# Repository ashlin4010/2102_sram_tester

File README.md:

# 2102 SRAM Tester #

A basic tester to quickly check 2102 RAM chips. This tester only performs rudimentary tests and is very lax with its timing so it may not fully detect marginal RAM chips.

## Firmware ##
The firmware is a quick and dirty Arduino program and makes use of `digitalWrite` and is subsequently very slow. Things could be sped up significantly by writing the firmware in AVR and using timers and cycle counting. The circuit would also benefit from an external latch for the address lines.

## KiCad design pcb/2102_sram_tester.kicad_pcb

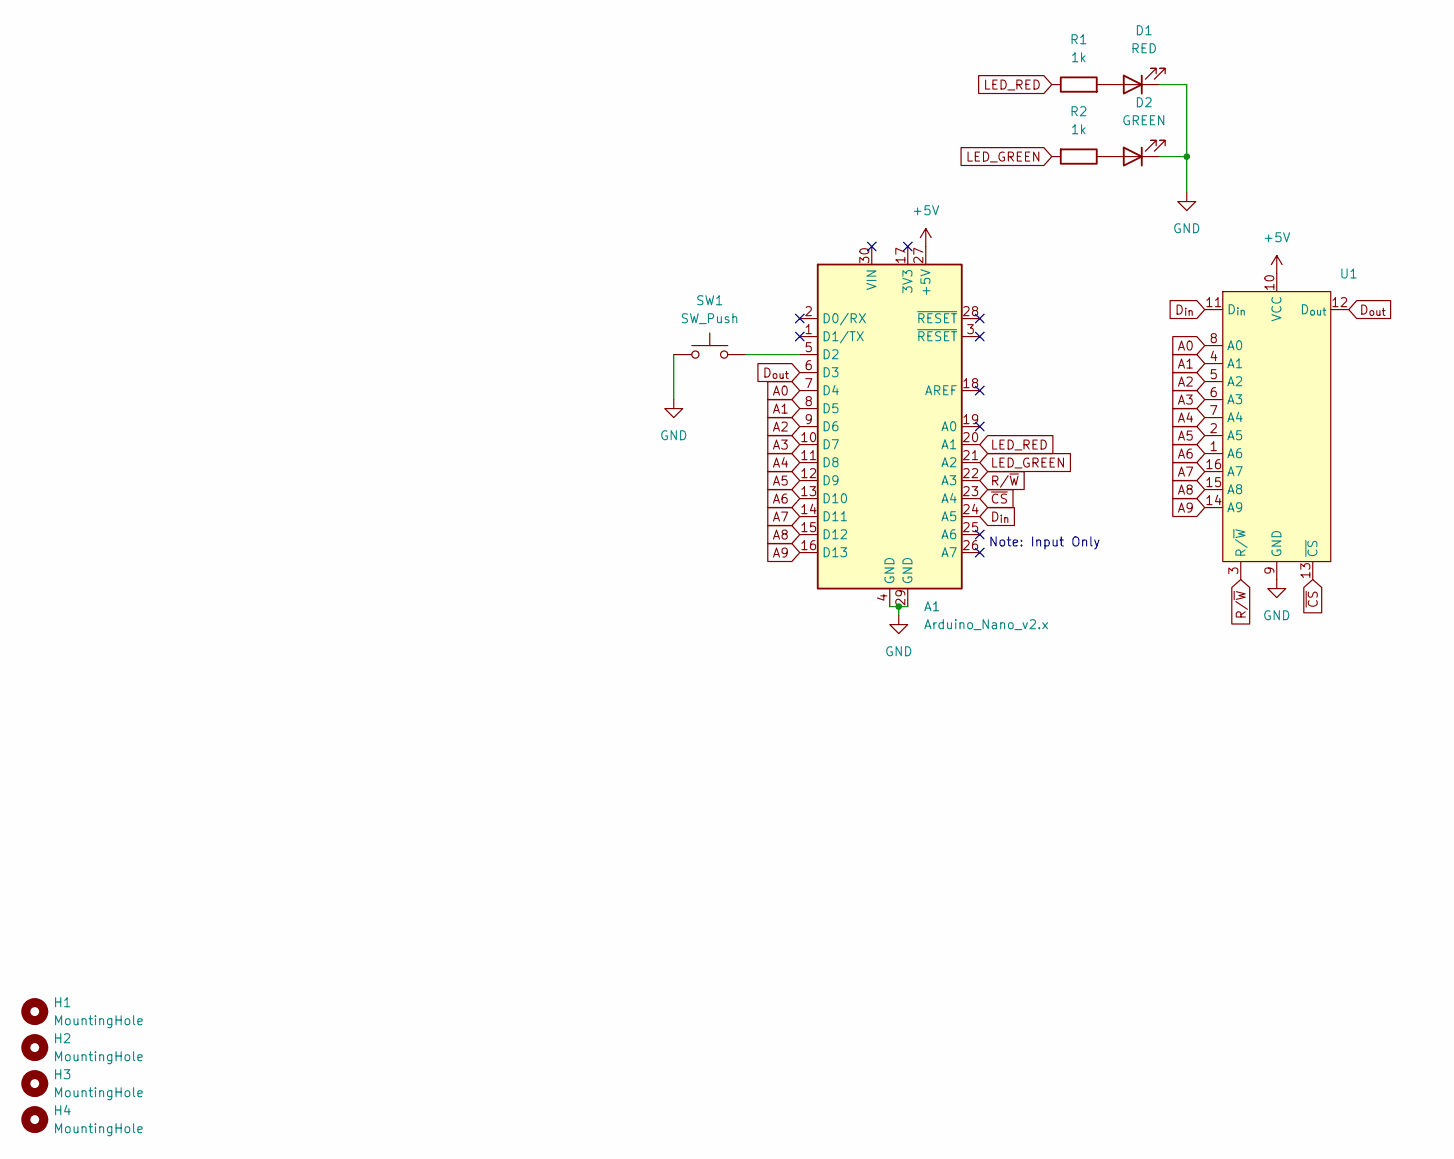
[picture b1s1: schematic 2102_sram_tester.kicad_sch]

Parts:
A1: Arduino_Nano_v2.x; Arduino_Nano
D1: RED; LED_D3.0mm
D2: GREEN; LED_D3.0mm
H1, H2, H3, H4: MountingHole; MountingHole_3.2mm_M3
R1, R2: 1k; R_Axial_DIN0204_L3.6mm_D1.6mm_P7.62mm_Horizontal
SW1: SW_Push; SW_PUSH_6mm
U1: DIP_Socket-16_W4.3_W5.08_W7.62_W10.16_W10.9_3M_216-3340-00-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

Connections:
+5V: A1.27 (+5V), U1.10 (VCC)
A0: A1.7 (D4), U1.8 (A0)
A1: A1.8 (D5), U1.4 (A1)
A2: A1.9 (D6), U1.5 (A2)
A3: A1.10 (D7), U1.6 (A3)
A4: A1.11 (D8), U1.7 (A4)
A5: A1.12 (D9), U1.2 (A5)
A6: A1.13 (D10), U1.1 (A6)
A7: A1.14 (D11), U1.16 (A7)
A8: A1.15 (D12), U1.15 (A8)
A9: A1.16 (D13), U1.14 (A9)
D_{in}: A1.24 (A5), U1.11 (D_{in})
D_{out}: A1.6 (D3), U1.12 (D_{out})
GND: A1.4 (GND), A1.29 (GND), D1.1 (K), D2.1 (K), SW1.1, U1.9 (GND)
LED_GREEN: A1.21 (A2), R2.2
LED_RED: A1.20 (A1), R1.1
unnamed: A1.5 (D2), SW1.2
unnamed: D1.2 (A), R1.2
unnamed: D2.2 (A), R2.1
R/~W: A1.22 (A3), U1.3 (R/~W)
~CS: A1.23 (A4), U1.13 (~CS)

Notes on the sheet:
Note: Input Only

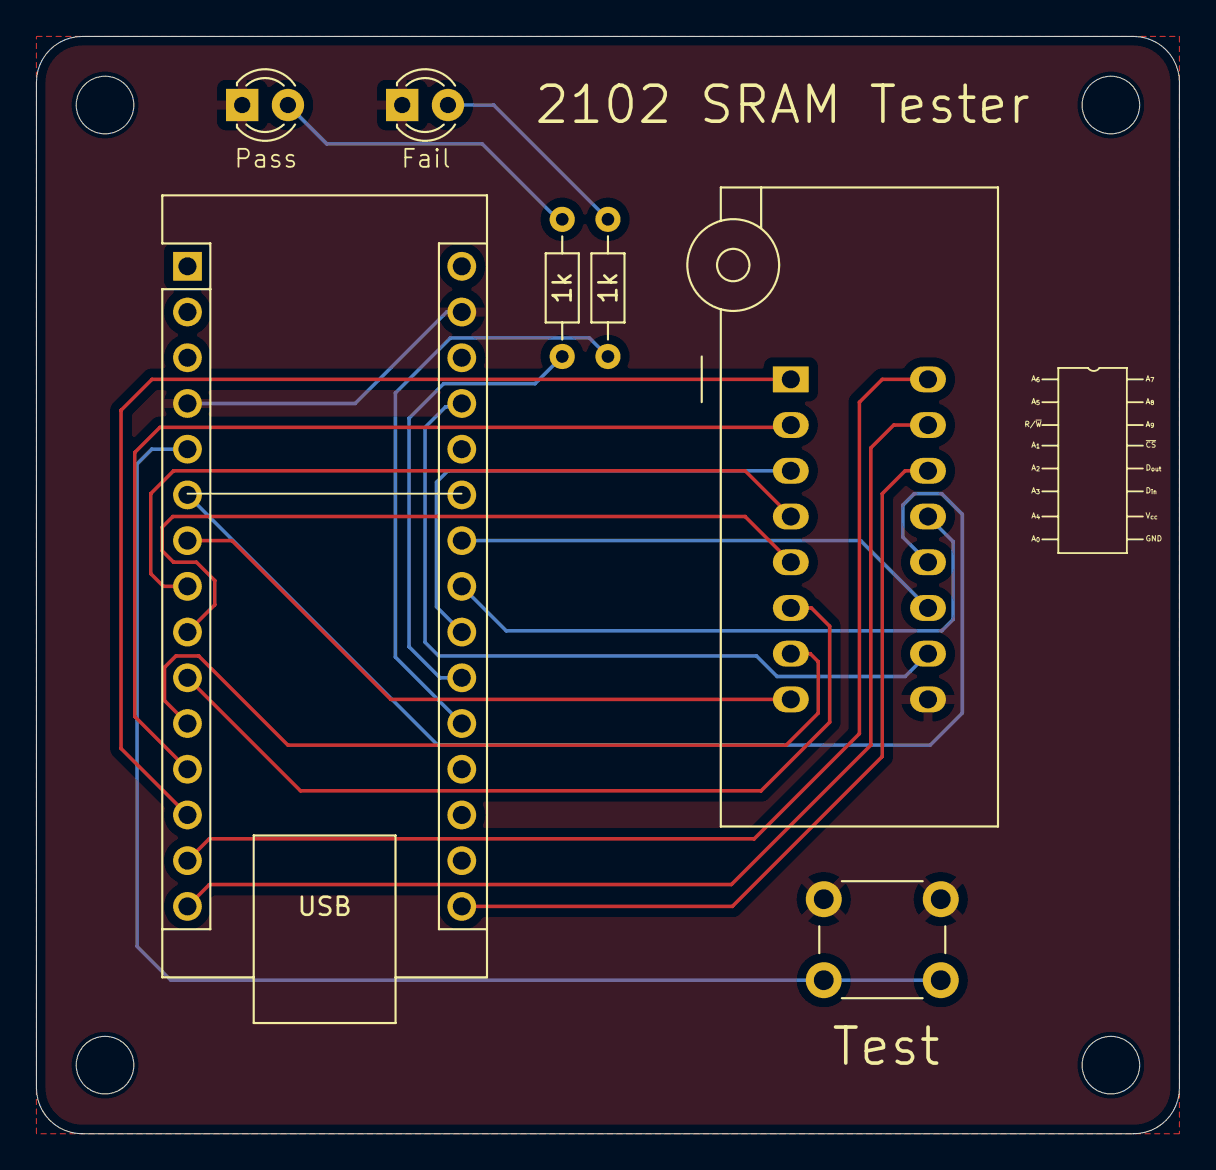
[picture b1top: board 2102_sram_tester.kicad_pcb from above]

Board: 2 copper layers, 63.5 x 61.0 mm, 11 parts (0 on the bottom side), 21 nets.

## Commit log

2025-02-12 init
2025-02-14 Added firmware and updated PCB
